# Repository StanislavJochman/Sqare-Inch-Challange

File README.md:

# Sqare-Inch-Challange
This Github Repository is for ESP8266 device which can measure data from sensors and upload them on GoogleDrive Sheets. Footprint of this device is 1x1 inch(25.4mm x 25.4mm)

## Order PCB
[OSH park](https://oshpark.com/shared_projects/sk7W7fMs)

## Komponents needed
* [PCB](https://raw.githubusercontent.com/StanislavJochman/Sqare-Inch-Challange/master/Gerber_Files.zip)
* [ESP8266](https://www.ebay.co.uk/itm/Profession-Esp-12E-ESP8266-Serial-Port-WIFI-Transceiver-Wireless-Module-AP-STA/163158011629?epid=16021614732&hash=item25fcf9aeed:g:bIIAAOSwK-NbUZIL)
* [DS18B20](https://www.ebay.co.uk/itm/DS18B20-TO-92-9-12bit-Temperature-Sensor-Dallas-Thermometer-Temperature-Sensor/291950339086?hash=item43f998a40e:m:m4YO8sV3_vF_5mhnVRi-43A)
* [DHT22](https://www.ebay.co.uk/itm/1-2-5-10PCS-DHT22-AM2302-Temperature-Humidity-Sensor-Replace-SHT11-SHT15-Module/272484297869?hash=item3f71546c8d:m:mGt9gF2SrPUPrgvcAIzpEHg)
* [BMP180](https://www.ebay.com/itm/NEW-BMP180-BOSCH-Pressure-sensor-LGA-7-GOOD-QUALITY/282770708207?hash=item41d67296ef%3Ag%3AHU4AAOSwZVlXoU2x&_sacat=0&_nkw=BOSCH+BMP180&_from=R40&rt=nc&_trksid=m570.l1313)/[BMP180 Module](https://www.ebay.co.uk/itm/BMP180-Replace-BMP085-Digital-Barometric-Pressure-Sensor-Board-Module-f-EA/362322141662?epid=3019497702&hash=item545c1521de:g:IggAAOSwo9Va~OUp)
* [LDR](https://www.ebay.co.uk/itm/10PCS-Photoresistor-LDR-CDS-5mm-Resistor-Sensor-Light-Dependent-GL5516-ATF/192428070436?epid=516237872&hash=item2ccd9b5624:g:7NgAAOSwa0VaAinj)
* [2 x 100n capacitor (0805)](https://www.ebay.co.uk/itm/50pcs-Case-0805-SMD-Capacitor-50V-100NF-10-X7R-CL21B104KBCNNNC/401367378177?hash=item5d735c2901:g:emAAAOSwbw1aHC90)
* [2 x 10k resistor(0805)](https://www.ebay.co.uk/itm/100Pcs-Resistor-10K-Ohm-0805-Smd-Rohs-New-Ic/382469082086?hash=item590cef0be6:g:858AAOSwxblbQlc-)
* [2 x 4k7 resistor(0805)](https://www.ebay.co.uk/itm/100Pcs-Resistor-4K7-Ohm-0805-Smd-Rohs-Ic-New/132176766970?hash=item1ec65967fa:g:0ncAAOSwDcZbPfAu)
* [1 x 1k resistor(0805)](https://www.ebay.co.uk/itm/100Pcs-0805-Smd-Smt-1K-1Kohn-Value-5-Resistor-New-Ic/382469059974?hash=item590ceeb586:g:~JoAAOSwl~ZbQlSN)
## Price calculation
| Component             | Price per 3 units |
|-----------------------|:-----------------:|
| PCB                   |         5$        |
| ESP8266               |       6.09$       |
| DS18B20               |       3,78$       |
| DHT22                 |       8,34$       |
| BMP180/BMP180 Modul   |     5.4$/3,78$    |
| LDR                   |       1.26$       |
| 100n capacitor (0805) |       3.31$       |
| 10k resistors (0805)  |       1.26$       |
| 1k resistors (0805)   |       1.26$       |
| 4k7 resistors (0805)  |       1.26$       |
|-----------------------|-------------------|
| Total:                |  36,96$ / 35,34$  |

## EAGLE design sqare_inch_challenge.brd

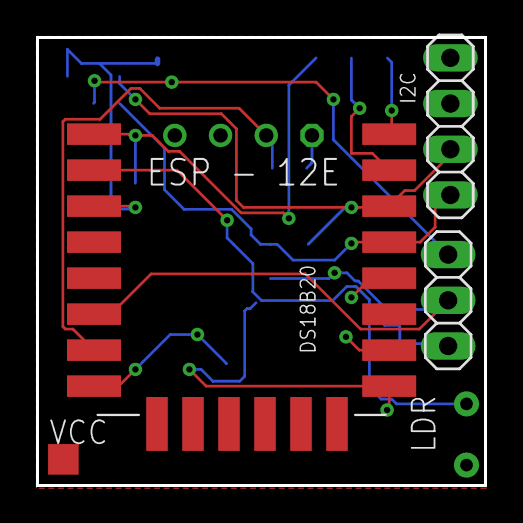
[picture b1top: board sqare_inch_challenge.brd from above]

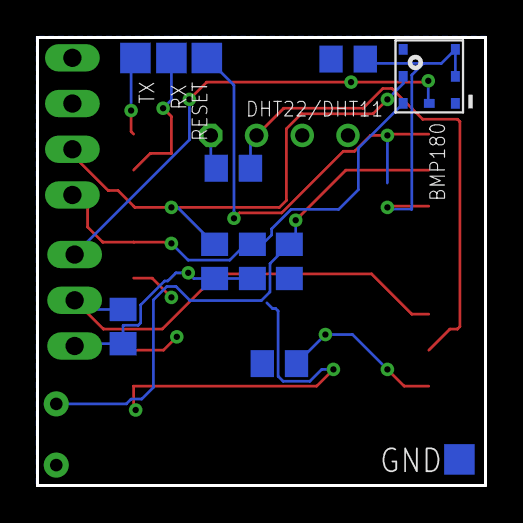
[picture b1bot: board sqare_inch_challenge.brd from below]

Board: 2 copper layers, 24.9 x 24.9 mm, 18 parts (13 on the bottom side), 10 nets.

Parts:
BMP180: BMP180
C1, C2: 100n; C0805
DHT22/DHT11: RHT03_DHT-22
DS18B20: 1X03
GND: GND; TP17SQ
I2C: 1X04
LDR: LDR; T0-46-A10XX
R5, R6: 10k; R0805
R7: 1k; R0805
R8, R9: 4k7; R0805
RESET: PTR1TP17SQ; TP17SQ
RX: PTR1TP17SQ; TP17SQ
TX: PTR1TP17SQ; TP17SQ
U1: ESP12E-SMD
VCC: +3V3; TP17SQ

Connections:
1W: DS18B20.2, R8.1, U1.GPIO12
+3V3: BMP180.2, BMP180.3, C1.1, C2.1, DHT22/DHT11.VDD, DS18B20.3, I2C.1, LDR.1, R5.2, R6.2, R8.2, R9.2, U1.CH_PD, U1.VCC, VCC.TP
DHT: DHT22/DHT11.DATA, R9.1, U1.GPIO13
GND: BMP180.7, C1.2, C2.2, DHT22/DHT11.GND, DS18B20.1, GND.TP, I2C.2, R7.1, U1.GND, U1.GPIO0, U1.GPIO15
LDR: LDR.2, R7.2, U1.ADC
RESET: RESET.TP, U1.RESET
RX: RX.TP, U1.RXD0
SCL: BMP180.5, I2C.3, R6.1, U1.GPIO5
SDA: BMP180.6, I2C.4, R5.1, U1.GPIO4
TX: TX.TP, U1.TXD0

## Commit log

2018-08-11 Gerbers
    Gerbers for ESP8266 1inch square datalogger
2018-08-11 Board file
2018-08-11 Schematic
2018-08-11 Library of modified components
2018-08-11 Final version
2018-08-11 Final Schematic
2018-08-11 Final Board Files
2018-09-04 Gerber files
2018-09-04 Board files
2018-09-04 Schematic files
2018-09-07 Programs for ESP8266
2018-09-08 Program for datalogging (Google Sheets)
